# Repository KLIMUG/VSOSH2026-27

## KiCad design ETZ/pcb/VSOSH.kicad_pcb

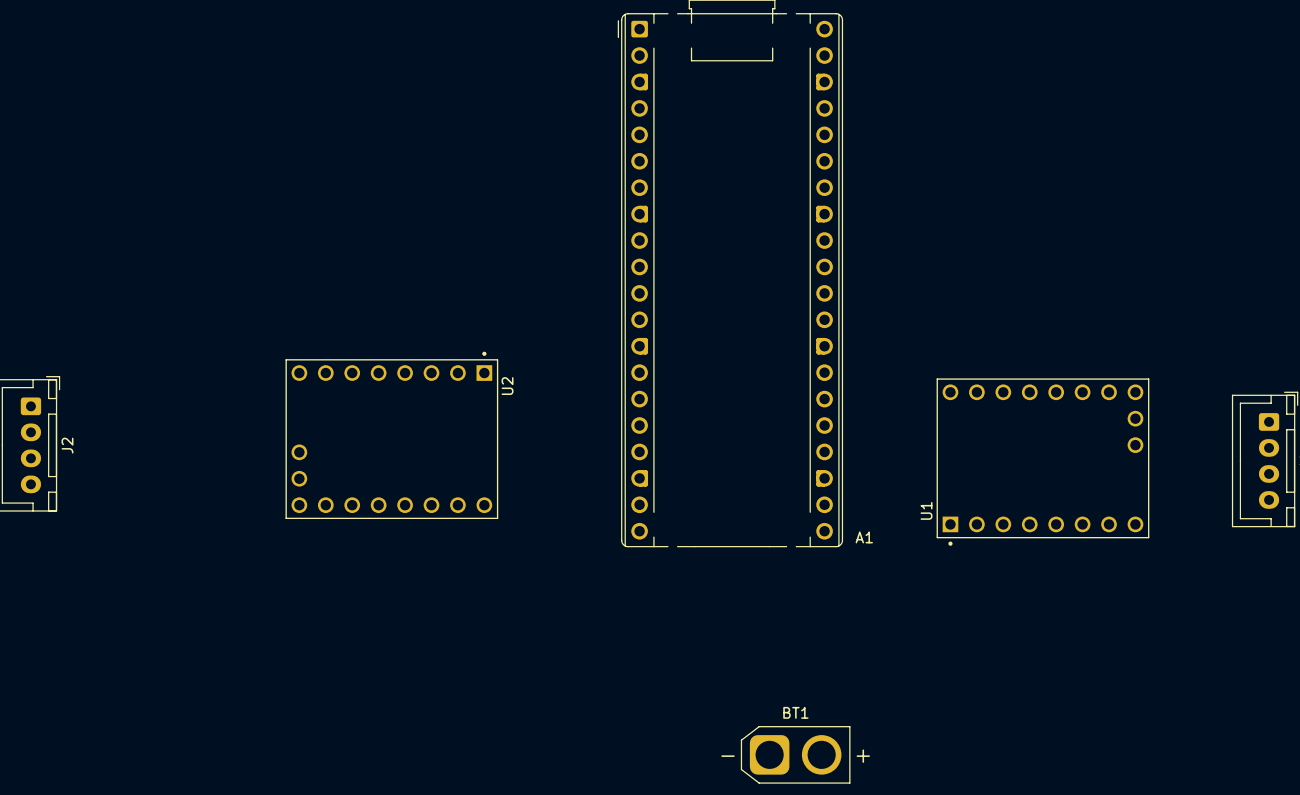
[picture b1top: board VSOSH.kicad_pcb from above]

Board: 2 copper layers, 6 parts (0 on the bottom side), 21 nets, no tracks yet.

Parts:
A1: RaspberryPi_Pico; RaspberryPi_Pico_Common_THT
BT1: 3s, 12в; AMASS_XT30U-M_1x02_P5.0mm_Vertical
J1: Y1_motor; JST_XH_B4B-XH-A_1x04_P2.50mm_Vertical
J2: Y2_motor; JST_XH_B4B-XH-A_1x04_P2.50mm_Vertical
U1: TMC2209_SILENTSTEPSTICK_Y1; MODULE_TMC2209_SILENTSTEPSTICK
U2: TMC2209_SILENTSTEPSTICK_Y2; MODULE_TMC2209_SILENTSTEPSTICK

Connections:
+3.3V: A1.36 (3V3), U1.2 (VIO), U2.2 (VIO)
+12V: BT1.1 (+), U1.8 (VM), U2.8 (VM)
GND: A1.3 (GND), A1.8 (GND), A1.13 (GND), A1.18 (GND), A1.23 (GND), A1.28 (GND), A1.38 (GND), BT1.2 (-), U1.1 (GND), U1.7 (GND), U2.1 (GND), U2.7 (GND)
unnamed: A1.15 (GPIO11), U2.18 (DIAG)
unnamed: A1.16 (GPIO12), U2.10 (STEP)
unnamed: A1.17 (GPIO13), U2.9 (DIR)
unnamed: A1.19 (GPIO14), U2.15 (MS1)
unnamed: A1.20 (GPIO15), U2.14 (MS2)
unnamed: A1.21 (GPIO16), U1.10 (STEP)
unnamed: A1.22 (GPIO17), U1.9 (DIR)
unnamed: A1.24 (GPIO18), U1.15 (MS1)
unnamed: A1.25 (GPIO19), U1.14 (MS2)
unnamed: A1.26 (GPIO20), U1.18 (DIAG)
unnamed: J1.1, U1.4 (M1A)
unnamed: J1.2, U1.5 (M2A)
unnamed: J1.3, U1.3 (M1B)
unnamed: J1.4, U1.6 (M2B)
unnamed: J2.1, U2.4 (M1A)
unnamed: J2.2, U2.5 (M2A)
unnamed: J2.3, U2.3 (M1B)
unnamed: J2.4, U2.6 (M2B)
